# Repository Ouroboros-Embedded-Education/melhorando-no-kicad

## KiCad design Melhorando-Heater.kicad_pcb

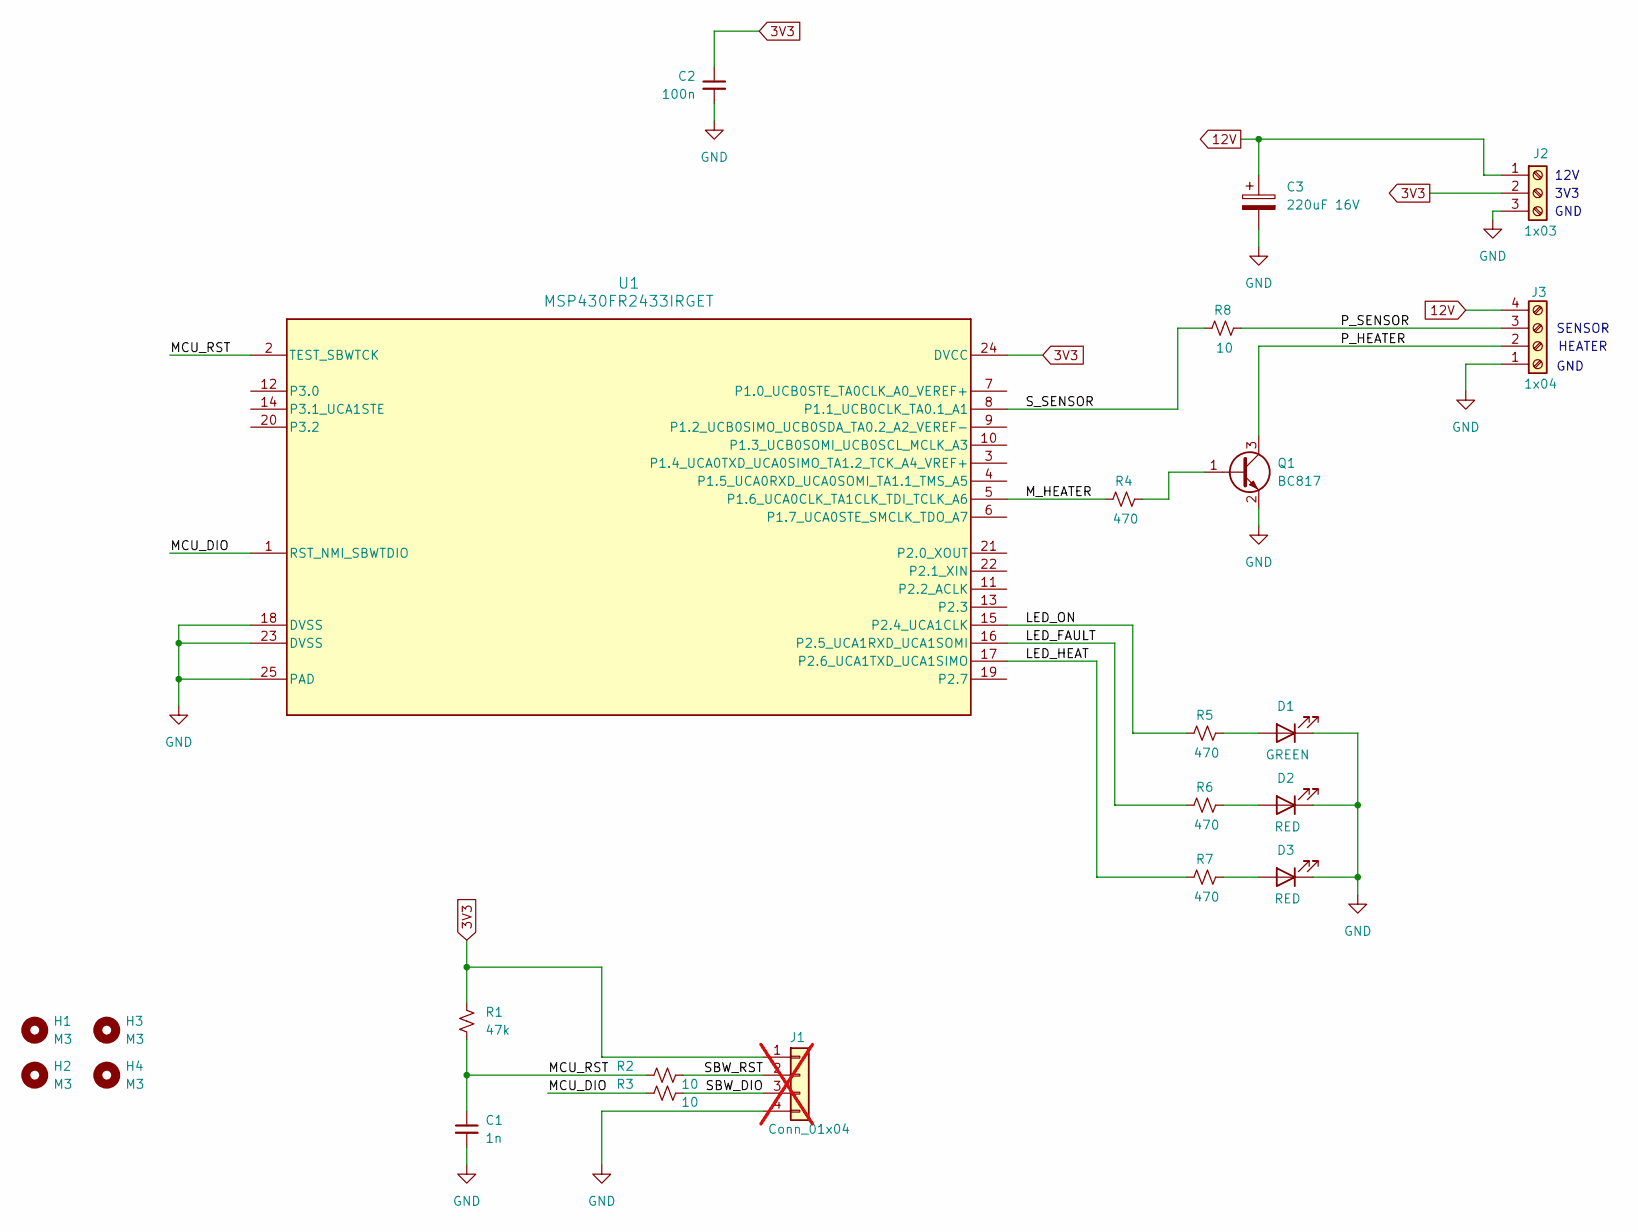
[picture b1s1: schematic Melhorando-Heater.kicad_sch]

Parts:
C1: 1n; C_0603_1608Metric; MPN CC0603KRX7R9BB102; LCSC C100040
C2: 100n; C_0603_1608Metric; MPN CC0603KRX7R9BB104; LCSC C14663
C3: 220uF 16V; CP_Elec_6.3x5.2
D1: GREEN; LED_0805_2012Metric
D2, D3: RED; LED_0805_2012Metric
H1, H2, H3, H4: M3; MountingHole_3.2mm_M3
J1: Conn_01x04; PinSocket_1x04_P2.54mm_Vertical; not fitted
J2: 1x03; TerminalBlock_Phoenix_MKDS-1,5-3-5.08_1x03_P5.08mm_Horizont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
J3: 1x04; TerminalBlock_Phoenix_MKDS-1,5-4-5.08_1x04_P5.08mm_Horizont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
Q1: BC817; SOT-23
R1: 47k; R_0603_1608Metric; MPN RC0603FR-0747KL; LCSC C105579
R2, R3, R8: 10; R_0603_1608Metric; MPN RC0603FR-0710RL; LCSC C109318
R4, R5, R6, R7: 470; R_0603_1608Metric; MPN RC0603FR-0710RL; LCSC C109318
U1: MSP430FR2433IRGET; VQFN-24-1EP_4x4mm_P0.5mm_EP2.45x2.45mm; MPN MSP430FR2433IRGET; LCSC C191026

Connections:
3V3: C2.1, J1.1, J2.2, R1.1, U1.24 (DVCC)
12V: C3.1, J2.1, J3.4
/LED_FAULT: R6.1, U1.16 (P2.5_UCA1RXD_UCA1SOMI)
/LED_HEAT: R7.1, U1.17 (P2.6_UCA1TXD_UCA1SIMO)
/LED_ON: R5.1, U1.15 (P2.4_UCA1CLK)
/MCU_DIO: R3.1, U1.1 (RST_NMI_SBWTDIO)
/MCU_RST: C1.1, R1.2, R2.1, U1.2 (TEST_SBWTCK)
/M_HEATER: R4.1, U1.5 (P1.6_UCA0CLK_TA1CLK_TDI_TCLK_A6)
/P_HEATER: J3.2, Q1.3 (C)
/P_SENSOR: J3.3, R8.2
/SBW_DIO: J1.3, R3.2
/SBW_RST: J1.2, R2.2
/S_SENSOR: R8.1, U1.8 (P1.1_UCB0CLK_TA0.1_A1)
GND: C1.2, C2.2, C3.2, D1.1 (K), D2.1 (K), D3.1 (K), J1.4, J2.3, J3.1, Q1.2 (E), U1.18 (DVSS), U1.23 (DVSS), U1.25 (PAD)
unnamed: D1.2 (A), R5.2
unnamed: D2.2 (A), R6.2
unnamed: D3.2 (A), R7.2
unnamed: Q1.1 (B), R4.2

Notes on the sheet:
GND
HEATER
SENSOR
12V
3V3

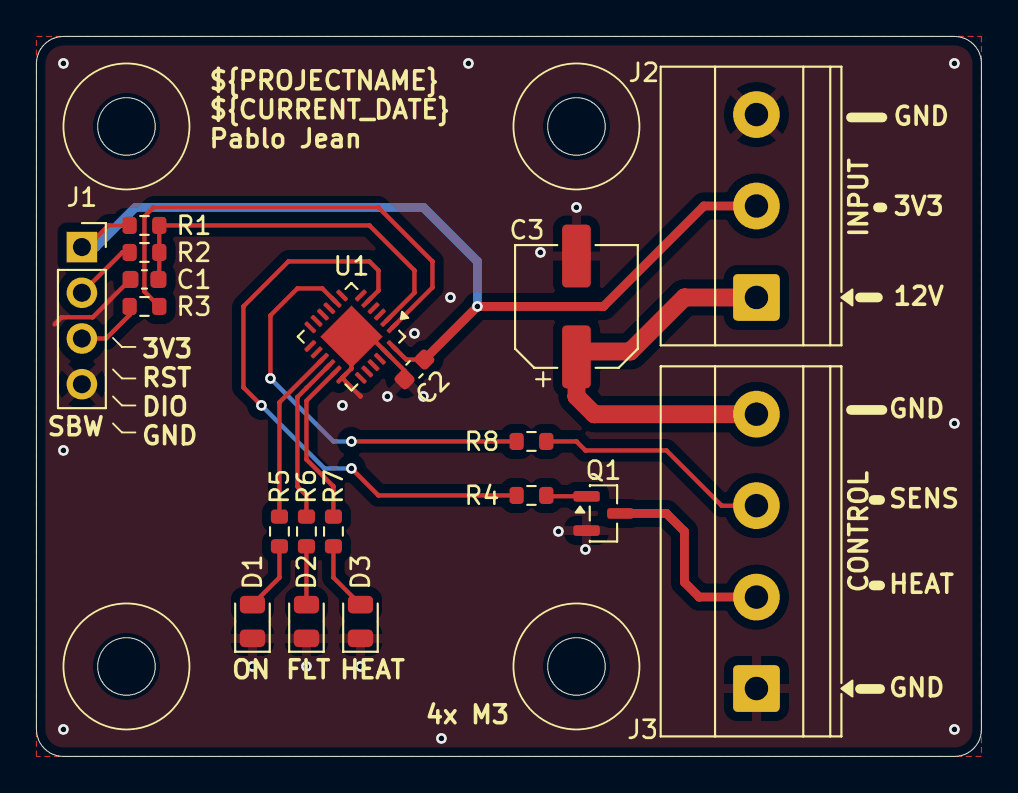
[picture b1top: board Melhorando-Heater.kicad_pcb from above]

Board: 2 copper layers, 52.5 x 40.0 mm, 23 parts (0 on the bottom side), 18 nets.

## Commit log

2026-01-08 :tada: created project
2026-01-08 :minidisc: finalizada placa problemática
2026-01-09 :minidisc: delivered finished board
